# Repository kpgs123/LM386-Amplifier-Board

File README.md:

# LM386-Amplifier-Board
Design simple LM386 amplifier PCB using KiCad 7.0

Schematic - 
Credit - JohnAudioTech - https://youtu.be/P4GsoMTv-SY

Build of Materials(BOM) -<br>

Board Layout -<br>
  Board Top -

  Board Bottom -

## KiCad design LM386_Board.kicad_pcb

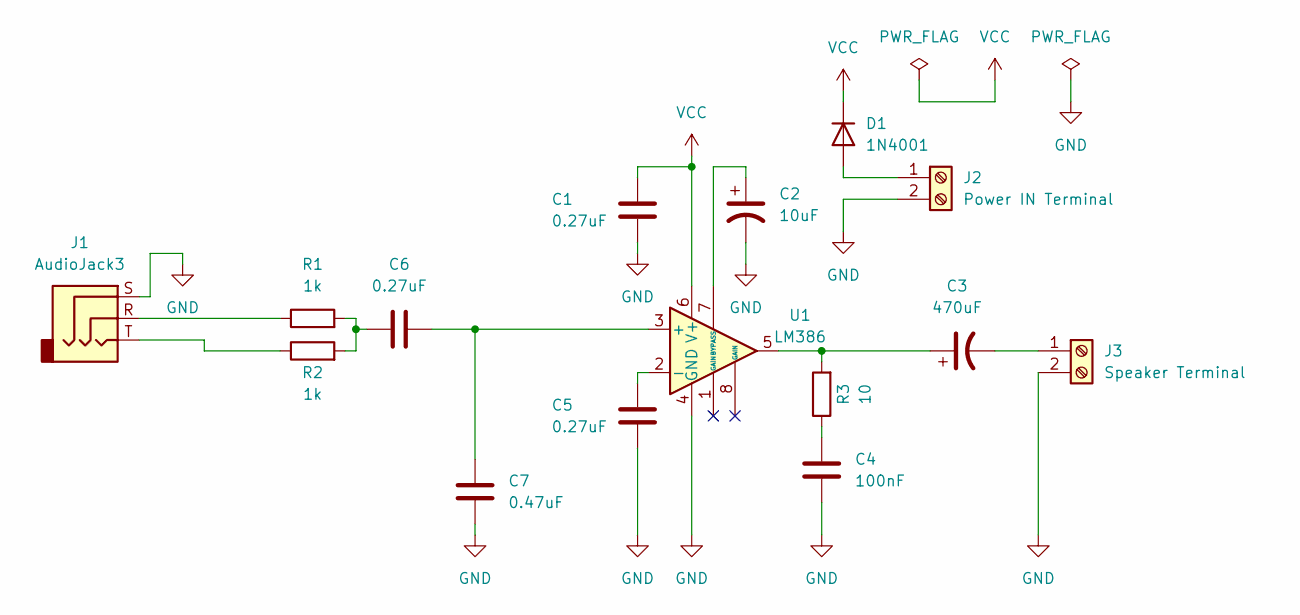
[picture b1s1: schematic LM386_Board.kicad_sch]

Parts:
C1, C5, C6: 0.27uF; C_Rect_L18.0mm_W6.0mm_P15.00mm_FKS3_FKP3
C2: 10uF; CP_Radial_D4.0mm_P1.50mm
C3: 470uF; CP_Radial_D10.0mm_P5.00mm
C4: 100nF; C_Rect_L7.2mm_W2.5mm_P5.00mm_FKS2_FKP2_MKS2_MKP2
C7: 0.47uF; C_Rect_L7.2mm_W4.5mm_P5.00mm_FKS2_FKP2_MKS2_MKP2
D1: 1N4001; D_DO-41_SOD81_P10.16mm_Horizontal
J1: AudioJack3; Jack_3.5mm_CUI_SJ-3523-SMT_Horizontal
J2: Power IN Terminal; TerminalBlock_MetzConnect_Type086_RT03402HBLC_1x02_P3.81mm_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
J3: Speaker Terminal; TerminalBlock_MetzConnect_Type086_RT03402HBLC_1x02_P3.81mm_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
R1, R2: 1k; R_Axial_DIN0207_L6.3mm_D2.5mm_P7.62mm_Horizontal
R3: 10; R_Axial_DIN0207_L6.3mm_D2.5mm_P7.62mm_Horizontal
U1: LM386; DIP-8_W7.62mm

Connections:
GND: C1.1, C2.2, C4.2, C5.2, C7.1, J1.S, J2.2, J3.2, U1.4 (GND)
unnamed: C3.1, R3.2, U1.5
unnamed: C4.1, R3.1
unnamed: C6.1, R1.2, R2.2
unnamed: D1.2 (A), J2.1
unnamed: J1.R, R1.1
unnamed: J1.T, R2.1
unnamed: C3.2, J3.1
unnamed: C6.2, C7.2, U1.3 (+)
unnamed: C5.1, U1.2 (-)
unnamed: C2.1, U1.7 (BYPASS)
VCC: C1.2, D1.1 (K), U1.6 (V+)

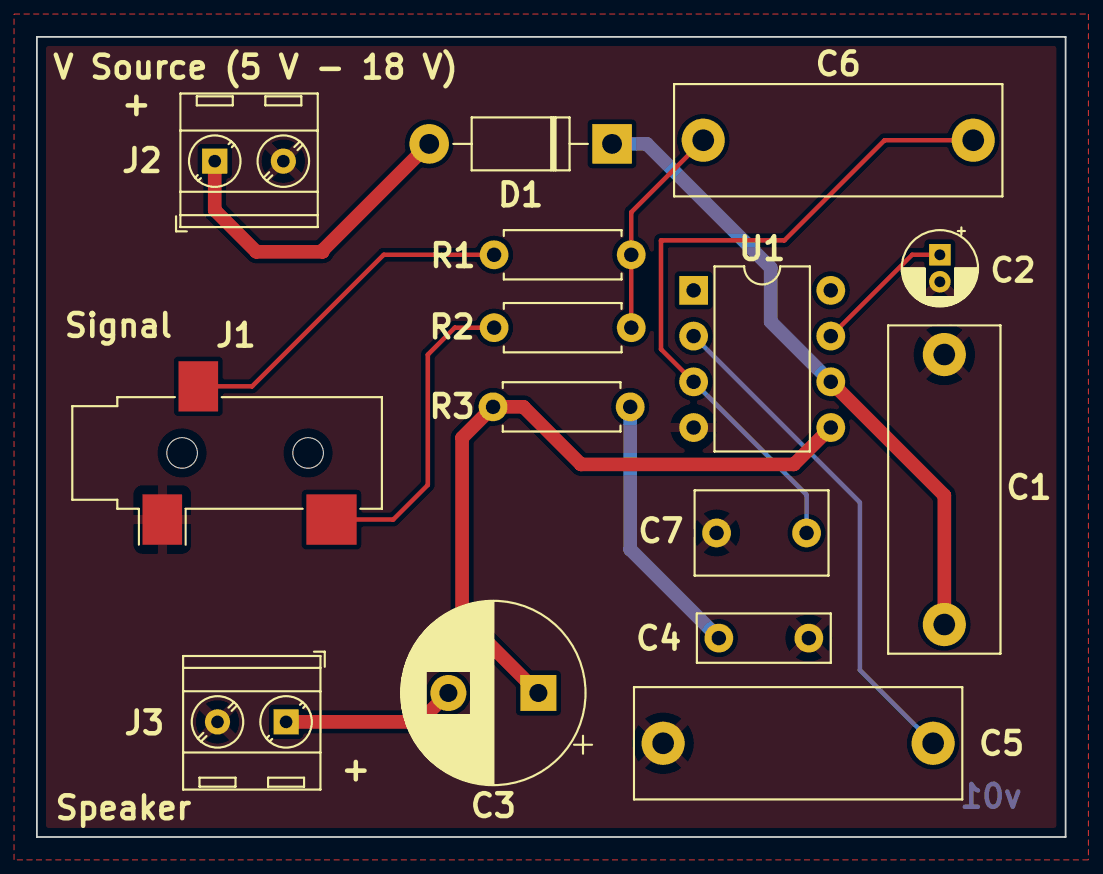
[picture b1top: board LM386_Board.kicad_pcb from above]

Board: 2 copper layers, 57.2 x 44.5 mm, 15 parts (0 on the bottom side), 12 nets.

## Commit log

2023-11-29 add all the files
2023-11-29 Update README.md
    Add pictures
2023-11-29 Update README.md
    edit1

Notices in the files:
LM386_Board.kicad_pcb:
creativecommons.org/licenses/by/4.0
License: CC BY 4.0
